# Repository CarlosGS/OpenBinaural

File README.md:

# OpenBinaural 3D microphone design
Low-cost 3D-printable binaural microphone.  

Project presented at [**OSHWDem 2015**](http://oshwdem.org/) (Open Source Hardware Demonstration in A Coruña, Spain) and [**Maker Faire Bilbao 2015**](http://bilbaomakerfaire.com/meet-the-makers-2015/). First featured in [**Hackaday**](http://hackaday.com/2015/06/28/3d-printing-binaural-microphones/).

Assembly instructions
--
[**Click here for the full assembly instructions**](https://github.com/carlosgs/OpenBinaural/wiki)  

Demo recordings
--
* By [Philippe Benaim](https://www.youtube.com/channel/UCL3Ne8XJYRqAHHRvmHdczcw):
 * Un tour Montgolfière [(link)](https://www.youtube.com/watch?v=H2nlUVNs7Po)
 * Château de Chenonceau Outside [(link)](https://www.youtube.com/watch?v=rT2So4uhhjw)
 * Vacances Aout 2015 [(link)](https://www.youtube.com/watch?v=p6LAYfAAe6M)
* By Carlosgs:
 * Sea shore in A Coruña, Spain [(link)](https://www.youtube.com/watch?v=49GC-DsRlKY)
* If you use the mic, please let me know, I'd love to *hear* about it! :-)

Assembled OpenBinaural microphone:  

3D-printable ears  
--
The [left](binaural_mic_left.stl) and [right](binaural_mic_right.stl) ears, and the [potentiometer knob](potentiometer_knob.stl) can be 3D-printed in PLA or ABS. Flexible materials may create more realistic effects!  
The support for the ears can be laser-cut out of 3mm plywood ([DXF file](wood_support.dxf)) or 3D printed ([STL file](wood_support_assembled_simplified.stl)).

Tripod mount detail:  
  
The metal insert can be found in eBay as *1/4" to 3/8" convert screw*  

Electronics  
--

**Note: The amplifier circuit is very outdated and noisy! Instead I recommend connecting the microphone capsules directly to the recorder. See [here](https://github.com/carlosgs/OpenBinaural/wiki#if-you-have-a-gopro-you-dont-need-the-amplifier-circuit) for an example.**

The KiCad sources for the electronics can be found in the [Electronics](Electronics) folder.  
Here are the [schematic](Electronics/stereo_mic_amplifier.pdf) and [layout](Electronics/pictures/stereo_mic_amplifier_layout.png).  
The Gerber files, B/W layout in PDF, and CNC gcode files can be found [here](Electronics/Gerber).  

Detailed ear canal
--

Where to buy
--
I currently have no plans to sell this microphone, it has an open license so **anyone can build it or sell it** (as long as they provide attribution and publish their modifications as open too).  
Please refer to the following links if you just need a binaural microphone that works out of the box:  

- [**3Dio**](https://3diosound.com/)
- [**SR3D**](https://www.sr3d.co.uk/), [**Ebay**](https://www.ebay.co.uk/str/sr3dbinauralmicrophones)

Acknowledgments  
--
* The awesome ear model was designed by **Jonathan March**:  
<http://www.thingiverse.com/thing:499001>  
For this project, the STL was modified with [FreeCAD](http://freecadweb.org/) and [Blender](http://www.blender.org/)  

* Great inspiration was taken from [**3Dio**](http://3diosound.com/).
If you need professional quality & high-performance, check out their Free Space microphones!  

* The potentiometer knob model is derived from **John Ridley's**: <https://www.youmagine.com/designs/knob-for-potentiometer-parametric>

* I want to thank [**Imperial College Advanced Hackspace**](http://icah.org.uk/) and [**Imperial College Robotics Society**](http://icrobotics.co.uk/) for providing the infrastructure (tools, 3D printers, laser cutters & material resources) that made this project possible. The community that has grown upon them is just amazing.  

* Also thanks to Mr Rodrigo García Saura for sourcing the 1/4" to 3/8" convert screw for the tripod mount  

Author & license  
--
Author: Carlos Garcia Saura (<https://github.com/CarlosGS/>)  
License: CC-BY-SA (<http://creativecommons.org/licenses/by-sa/4.0/>)  

Please cite as:
--

Latex / Bibtex citation:

```bibtex
@misc{garciasaura2015binaural,
  author = {Garcia-Saura, Carlos},
  title = {Open Binaural 3D microphone design},
  publisher = {GitHub},
  year = {2015},
  doi = {10.5281/ZENODO.10446511},
  url = {https://doi.org/10.5281/ZENODO.10446511}
}
```

APA style citation:

- García-Saura, C. (2015). Open Binaural 3D microphone design. GitHub. https://doi.org/10.5281/ZENODO.10446511

Also check out my previous work _"3D Video with Binaural Audio"_:

- García-Saura, C. (2011). Vídeo en 3D con Sonido Binaural. Congreso del XXIV Certamen Jóvenes Investigadores INJUVE, CEULAJ Málaga. INJUVE. https://doi.org/10.5281/ZENODO.10445722

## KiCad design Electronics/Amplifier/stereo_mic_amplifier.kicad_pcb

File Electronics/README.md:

# Stereo microphone amplifier

Stereo microphone amplifier circuit with gain control.  

The circuit has been tested with the POM-5238P-R microphone capsules:  
<http://www.puiaudio.com/product-detail.aspx?categoryId=4&partnumber=POM-5238P-R>  

CNC manufacture files (gerbers, FlatCAM project & gcodes) are available in the [Gerber](Gerber) folder.  

Assembly instructions
--
[**Click here for the full assembly instructions**](https://github.com/carlosgs/OpenBinaural/wiki)  

Pictures  
--

[Download the schematic in PDF](stereo_mic_amplifier.pdf)  

Aprox milling time for 0.8mm drill: 4 minutes  

Aprox milling time for 1.2mm drill: 2 minutes  

Aprox milling time for 0.3mm copper etching: 20 minutes  

Aprox milling time for 2mm edges routing: 3 minutes  

Acknowledgments  
--
This circuit is a derivation from the following -very useful- Texas Instruments guide:  
[Single-Supply, Electret Microphone Preamplifier Reference Design](http://www.ti.com/tool/TIPD181) by John Caldwell  
Gain control is achieved by replacing R2 (75k) with a 100k dual potentiometer.  

Author & license  
--
Author: Carlos Garcia Saura (<http://www.carlosgs.es>)  
License: CC-BY-SA (<http://creativecommons.org/licenses/by-sa/4.0/>)

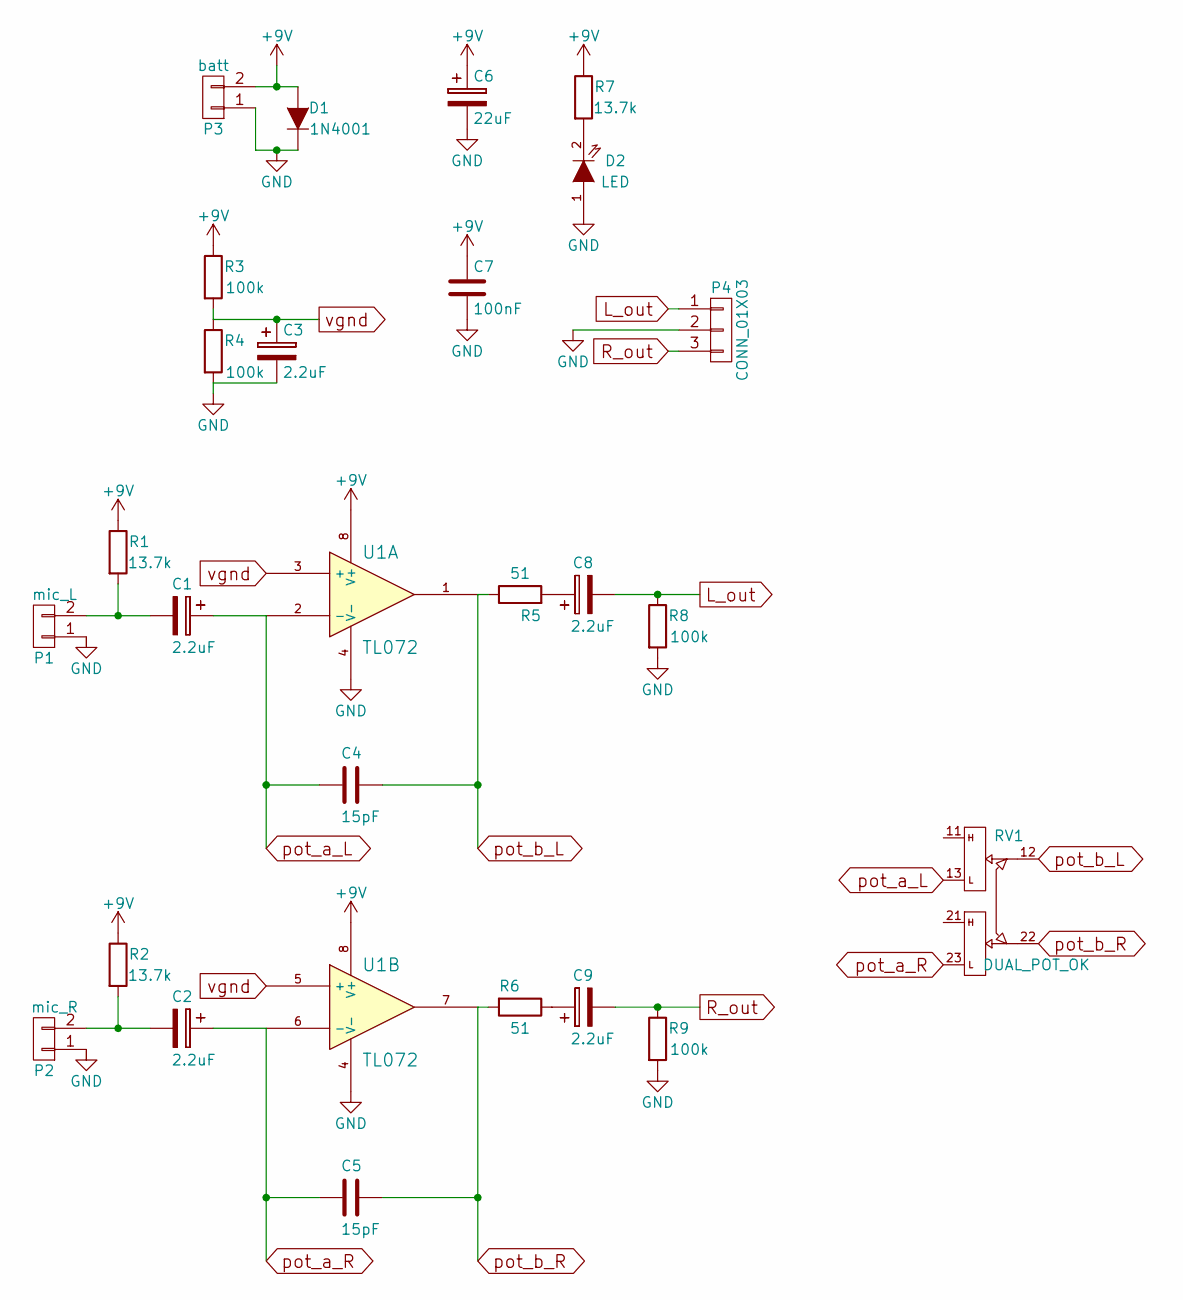
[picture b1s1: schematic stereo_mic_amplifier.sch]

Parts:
C1, C2, C3, C8, C9: 2.2uF; C1V8
C4, C5: 15pF; C_Disc_D7.5_P5
C6: 22uF; C1V8
C7: 100nF; C_Disc_D7.5_P5
D1: 1N4001; D3
D2: LED; LED-5MM
P1: mic_L; Pin_Header_Straight_1x02
P2: mic_R; Pin_Header_Straight_1x02
P3: batt; Pin_Header_Straight_1x02
P4: CONN_01X03; Pin_Header_Straight_1x03
R1, R2, R7: 13.7k; Resistor_Horizontal_RM10mm
R3, R4: 100k; Resistor_Horizontal_RM10mm
R5, R6: 51; Resistor_Vertical_RM5mm
R8, R9: 100k; Resistor_Vertical_RM5mm
RV1: DUAL_POT_OK; Potentiometer_Alps-RK163-double_15mm
U1: TL072; DIP-8__300_ELL

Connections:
+9V: C6.1, C7.1, D1.1 (A), P3.2, R1.1, R2.1, R3.1, R7.1, U1.8 (V+)
GND: C3.2, C6.2, C7.2, D1.2 (K), D2.1 (A), P1.1, P2.1, P3.1, P4.2, R4.2, R8.2, R9.2, U1.4 (V-)
L_out: C8.2, P4.1, R8.1
unnamed: C1.2, P1.2, R1.2
unnamed: C2.2, P2.2, R2.2
unnamed: C8.1, R5.2
unnamed: C9.1, R6.1
unnamed: D2.2 (K), R7.2
R_out: C9.2, P4.3, R9.1
pot_a_L: C1.1, C4.2, RV1.13, U1.2 (-)
pot_a_R: C2.1, C5.2, RV1.23, U1.6 (-)
pot_b_L: C4.1, R5.1, RV1.12, U1.1
pot_b_R: C5.1, R6.2, RV1.22, U1.7
vgnd: C3.1, R3.2, R4.1, U1.3 (+), U1.5 (+)

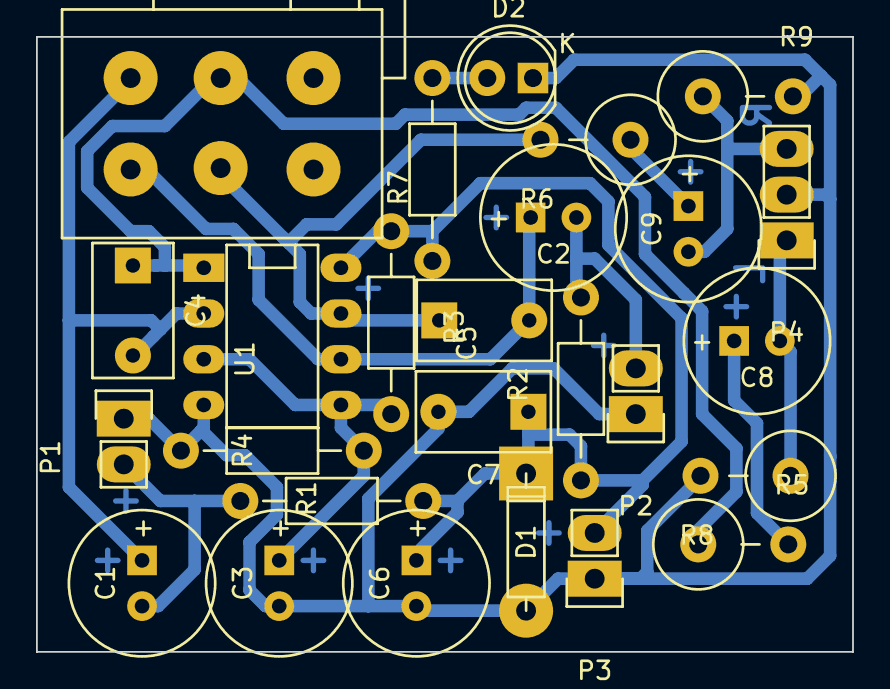
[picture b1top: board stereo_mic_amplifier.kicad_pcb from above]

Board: 2 copper layers, 45.3 x 34.2 mm, 26 parts (0 on the bottom side), 14 nets.

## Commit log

2015-05-10 Added details
2015-05-10 Added L/R files
2015-05-10 Repaired overhang
2015-05-10 updated left ear
2015-05-10 Updated ear size
2015-05-10 Updated credits
2015-05-11 Added bevel for microphone holder
2015-05-13 Improved ear canal & ear shape
2015-05-13 Updated figures
2015-05-15 Created laser-cuttable wood support
2015-05-16 updated STL
2015-05-16 Improved wood supports
2015-05-17 Added electronics folder
2015-05-17 Working version of the circuit
2015-05-17 backed up circuit
2015-05-18 Simplified polarization circuit
2015-05-18 Added picture
2015-05-18 Added link to sound test
2015-05-19 Added very interesting guide to polarize electret microphones
2015-05-21 Added link to 2nd test
2015-05-21 Updated electronics folder
2015-06-06 Added holes for potentiometer, LED & switch
2015-06-06 Added hole for audio cable strain relief (still need to render other files)
2015-06-06 Adjusted the dimensions of the wood support
2015-06-07 Added potentiometer knob
2015-06-09 Improved the design of the potentiometer knob
2015-06-09 Increased tolerance for potentiometer knob. Added some components to the schematic.
2015-06-11 Finished schematic
2015-06-12 Specified footprints
2015-06-12 Fixed dual potentiometer pins
2015-06-12 Deciding layout
2015-06-12 Fixing kicad libraries
2015-06-12 Work on the layout
2015-06-12 Increased pad sizes & improvements in layout
2015-06-12 Updated 3D picture
2015-06-13 backup
2015-06-13 Layout progress
2015-06-13 Finished layout
2015-06-13 Updated gerbers
2015-06-13 Added FlatCAM files for cnc manufacture
2015-06-13 Updated layout & cnc files
2015-06-13 Mirrored gcode
2015-06-13 rotated gerber
2015-06-13 Updated readme, plotted schematic, removed previous trials
2015-06-13 Swapped misplaced capacitor values
2015-06-14 Added pictures
2015-06-14 Re-arranged electronics directory
2015-06-14 Added electronics picture
2015-06-15 Removed unnecessary auto-level file
2015-06-21 Added times into CNC readme
2015-07-29 Fixed reversed diodes
2015-07-29 Added image with the schematic
2015-09-28 Updated readme, started assembly instructions
2015-09-28 Updated picture
2015-09-28 Added assembly steps
2015-09-28 Added links to OpenBinaural recordings
2015-09-28 Added mic polarity figure
2015-09-28 Added jack connector image, source http://www.akitarescueoftulsa.com/balanced-audio-wiring-diagram/
2015-09-28 Added more pictures
2015-10-27 Backup of version with self-threaded tripod mount
2015-10-27 Added version with metal insert tripod mount
2015-10-30 Increased diameter of tripod metal insert
2015-11-04 Created multi-pass gcode using bCNC
2015-11-09 Test of the new dimensions
2015-11-09 Rotated ears vertically, and increased ear support diameter, ear size, microphone diameter, and tripod mount diameter
2015-11-09 Updated README and picture
2015-11-09 Added links to binaural microphone sellers
2015-11-09 Added tripod mount image
2015-11-10 Gcode pass to Z-0.15mm
2015-11-26 Updated tolerance for the tripod metal thread insert
2020-05-07 Removed obsolete links
2023-12-31 Included DOI and Bibtex citation references, notes and simplified frame

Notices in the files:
Electronics/stereo_mic_amplifier.sch:
License: Attribution-ShareAlike 4.0 International (CC BY-SA 4.0)
